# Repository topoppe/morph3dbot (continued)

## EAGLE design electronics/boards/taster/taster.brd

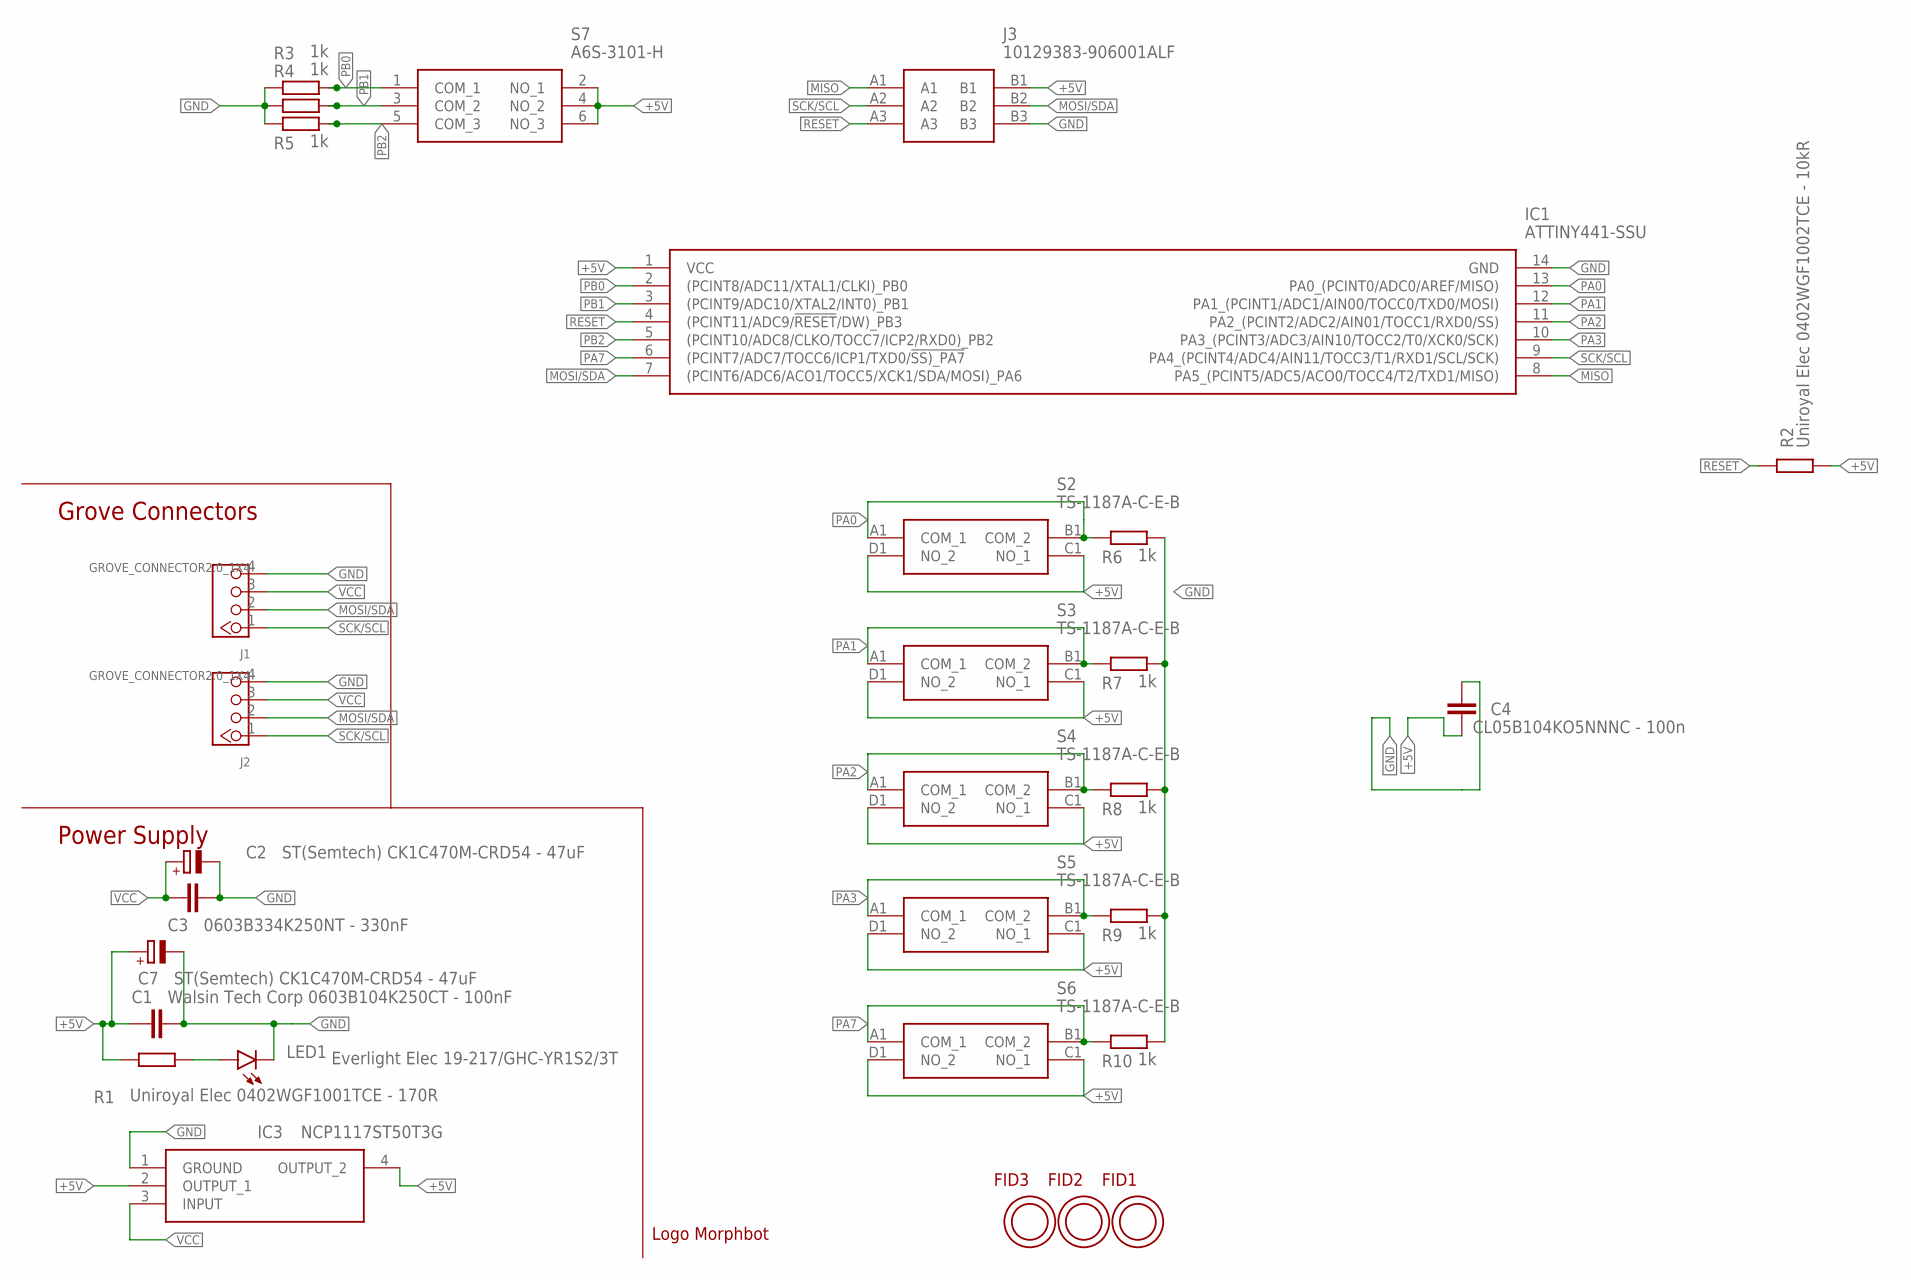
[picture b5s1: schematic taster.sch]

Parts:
C1: Walsin Tech Corp 0603B104K250CT - 100nF; C0603
C2, C7: ST(Semtech) CK1C470M-CRD54 - 47uF; PANASONIC_C
C3: 0603B334K250NT - 330nF; C0603
C4: CL05B104KO5NNNC - 100n; C0402
FID1, FID2, FID3: OPEN-PNP-FIDUCIAL
IC1: ATTINY441-SSU; SOIC127P600X175-14N
IC3: NCP1117ST50T3G; SOT230P700X180-4N
J1, J2: GROVE_CONNECTOR2.0_1X4; 2.0_1X4_STRAIGHT
J3: 10129383-906001ALF; 10129383906001ALF
LED1: Everlight Elec 19-217/GHC-YR1S2/3T; CHIPLED_0603
R1: Uniroyal Elec 0402WGF1001TCE - 170R; R0402
R2: Uniroyal Elec 0402WGF1002TCE - 10kR; R0402
R3, R4, R5, R6, R7, R8, R9, R10: 1k; R0402
S2, S3, S4, S5, S6: TS-1187A-C-E-B; TS1187ACEB
S7: A6S-3101-H; A6S3104H
U$1: LOGO_MORPHBOT5MM; LOGO_MORPHBOT

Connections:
+5V: C1.1, C4.1, C7.+, IC1.1 (VCC), IC3.2 (OUTPUT_1), IC3.4 (OUTPUT_2), J3.B1, R1.2, R2.2, S2.C1 (NO_1), S2.D1 (NO_2), S3.C1 (NO_1), S3.D1 (NO_2), S4.C1 (NO_1), S4.D1 (NO_2), S5.C1 (NO_1), S5.D1 (NO_2), S6.C1 (NO_1), S6.D1 (NO_2), S7.2 (NO_1), S7.4 (NO_2), S7.6 (NO_3)
GND: C1.2, C2.-, C3.1, C4.2, C7.-, IC1.14 (GND), IC3.1 (GROUND), J1.4, J2.4, J3.B3, LED1.C, R3.2, R4.2, R5.2, R6.1, R7.1, R8.1, R9.1, R10.1
MISO: IC1.8 (PA5_(PCINT5/ADC5/ACO0/TOCC4/T2/TXD1/MIS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), J3.A1
MOSI/SDA: IC1.7 ((PCINT6/ADC6/ACO1/TOCC5/XCK1/SDA/MOSI)_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), J1.2, J2.2, J3.B2
unnamed: LED1.A, R1.1
PA0: IC1.13 (PA0_(PCINT0/ADC0/AREF/MISO)), R6.2, S2.A1 (COM_1), S2.B1 (COM_2)
PA1: IC1.12 (PA1_(PCINT1/ADC1/AIN00/TOCC0/TXD0/MOSI)), R7.2, S3.A1 (COM_1), S3.B1 (COM_2)
PA2: IC1.11 (PA2_(PCINT2/ADC2/AIN01/TOCC1/RXD0/SS)), R8.2, S4.A1 (COM_1), S4.B1 (COM_2)
PA3: IC1.10 (PA3_(PCINT3/ADC3/AIN10/TOCC2/T0/XCK0/SC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), R9.2, S5.A1 (COM_1), S5.B1 (COM_2)
PA7: IC1.6 ((PCINT7/ADC7/TOCC6/ICP1/TXD0/!SS)_PA7), R10.2, S6.A1 (COM_1), S6.B1 (COM_2)
PB0: IC1.2 ((PCINT8/ADC11/XTAL1/CLKI)_PB0), R3.1, S7.1 (COM_1)
PB1: IC1.3 ((PCINT9/ADC10/XTAL2/INT0)_PB1), R4.1, S7.3 (COM_2)
PB2: IC1.5 ((PCINT10/ADC8/CLKO/TOCC7/ICP2/RXD0)_PB2), R5.1, S7.5 (COM_3)
RESET: IC1.4 ((PCINT11/ADC9/!RESET!/DW)_PB3), J3.A3, R2.1
SCK/SCL: IC1.9 (PA4_(PCINT4/ADC4/AIN11/TOCC3/T1/RXD1/SC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), J1.1, J2.1, J3.A2
VCC: C2.+, C3.2, IC3.3 (INPUT), J1.3, J2.3

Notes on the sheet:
Power Supply
Grove Connectors

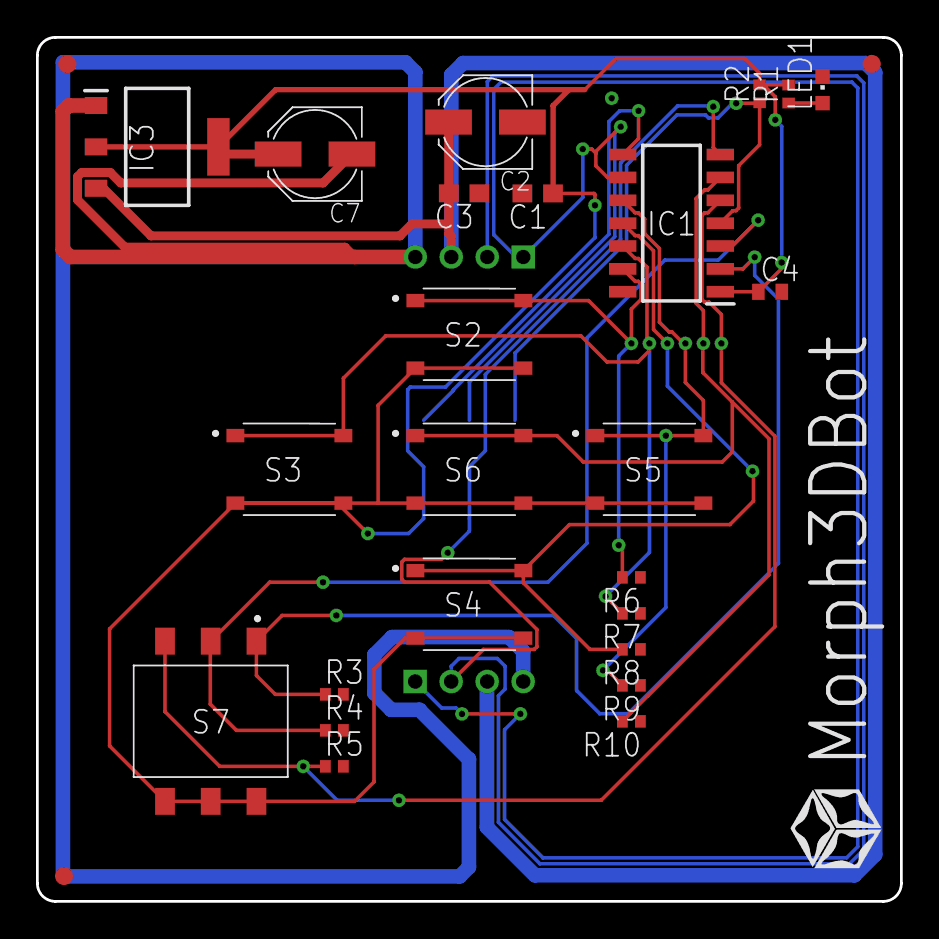
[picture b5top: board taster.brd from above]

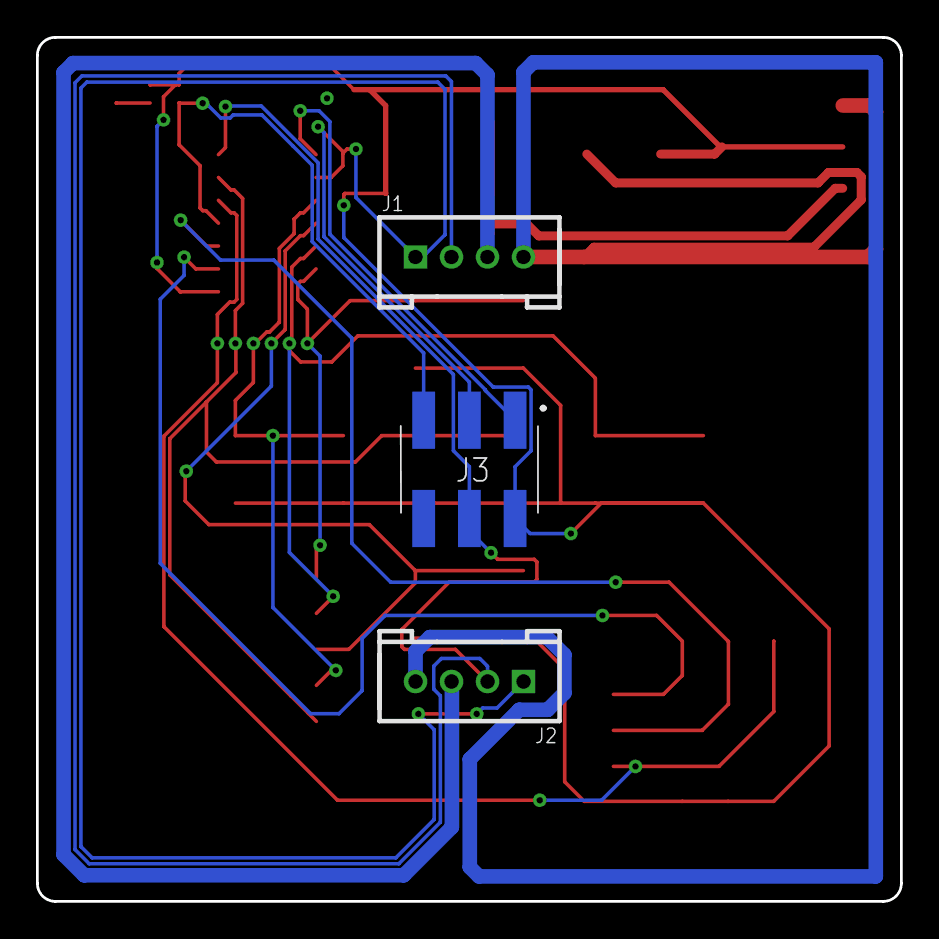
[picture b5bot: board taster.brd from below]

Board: 2 copper layers, 48.0 x 48.0 mm, 31 parts (3 on the bottom side), 16 nets.

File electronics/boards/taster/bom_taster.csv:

"Qty";"Value";"Device";"Package";"Parts";"Description";"ARROW_PART_NUMBER";"ARROW_PRICE-STOCK";"DESCRIPTION";"HEIGHT";"MANUFACTURER_NAME";"MANUFACTURER_PART_NUMBER";"MOUSER_PART_NUMBER";"MOUSER_PRICE-STOCK";"POPULARITY";"SPICEPREFIX";
"1";"0603B334K250NT - 330nF";"C-EUC0603";"C0603";"C3";"CAPACITOR, European symbol";"";"";"";"";"";"";"";"";"73";"C";
"1";"10129383-906001ALF";"10129383-906001ALF";"10129383906001ALF";"J3";"Headers & Wire Housings ECONOSTIK HEADER DR VT SMT 2X3";"10129383-906001ALF";"https://www.arrow.com/en/products/10129383-906001alf/amphenol-fci";"Headers & Wire Housings ECONOSTIK HEADER DR VT SMT 2X3";"8.58mm";"Amphenol";"10129383-906001ALF";"649-1012938390601ALF";"https://www.mouser.co.uk/ProductDetail/Amphenol-FCI/10129383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";"";"";
"8";"1k";"R-EU_R0402";"R0402";"R3, R4, R5, R6, R7, R8, R9, R10";"RESISTOR, European symbol";"";"";"";"";"";"";"";"";"0";"R";
"1";"A6S-3101-H";"A6S-3101-H";"A6S3104H";"S7";"3 Way Surface Mount DIP Switch 3P";"";"";"3 Way Surface Mount DIP Switch 3P";"4.5mm";"Omron Electronics";"A6S-3101-H";"653-A6S-3101-H";"https://www.mouser.co.uk/ProductDetail/Omron-Electronics/A6S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";"";"";
"1";"ATTINY441-SSU";"ATTINY441-SSU";"SOIC127P600X175-14N";"IC1";"8-bit Microcontrollers - MCU 16MHz 0.150" 14 SOIC";"ATTINY441-SSU";"https://www.arrow.com/en/products/attiny441-ssu/microchip-te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";"8-bit Microcontrollers - MCU 16MHz 0.150" 14 SOIC";"1.75mm";"Microchip";"ATTINY441-SSU";"556-ATTINY441-SSU";"https://www.mouser.co.uk/ProductDetail/Microchip-Technology-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";"";"";
"1";"CL05B104KO5NNNC - 100n";"C-EUC0402";"C0402";"C4";"CAPACITOR, European symbol";"";"";"";"";"";"";"";"";"18";"C";
"1";"Everlight Elec 19-217/GHC-YR1S2/3T";"LEDCHIPLED_0603";"CHIPLED_0603";"LED1";"LED";"";"";"";"";"";"";"";"";"28";"";
"2";"GROVE_CONNECTOR2.0_1X4";"GROVE_CONNECTOR2.0_1X4";"2.0_1X4_STRAIGHT";"J1, J2";"Seeedstudio Grove-Connector:";"";"";"";"";"";"";"";"";"";"";
"1";"LOGO_MORPHBOT5MM";"LOGO_MORPHBOT5MM";"LOGO_MORPHBOT";"U$1";"";"";"";"";"";"";"";"";"";"";"";
"1";"NCP1117ST50T3G";"NCP1117ST50T3G";"SOT230P700X180-4N";"IC3";"ON SEMICONDUCTOR - NCP1117ST50T3G - LDO, REG, 20VIN, 1A, 5V, 1%, SOT223-3";"NCP1117ST50T3G";"https://www.arrow.com/en/products/ncp1117st50t3g/on-semiconductor";"ON SEMICONDUCTOR - NCP1117ST50T3G - LDO, REG, 20VIN, 1A, 5V, 1%, SOT223-3";"1.8mm";"ON Semiconductor";"NCP1117ST50T3G";"863-NCP1117ST50T3G";"https://www.mouser.co.uk/ProductDetail/ON-Semiconductor/NCP1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";"";"";
"3";"OPEN-PNP-FIDUCIAL";"OPEN-PNP-FIDUCIAL";"OPEN-PNP-FIDUCIAL";"FID1, FID2, FID3";"";"";"";"";"";"";"";"";"";"";"";
"2";"ST(Semtech) CK1C470M-CRD54 - 47uF";"CPOL-EUC";"PANASONIC_C";"C2, C7";"POLARIZED CAPACITOR, European symbol";"";"";"";"";"";"";"";"";"4";"C";
"5";"TS-1187A-C-E-B";"TS-1187A-C-E-B";"TS1187ACEB";"S2, S3, S4, S5, S6";"SPST 50mA @ 12VDC 5.10mm x 5.10mm SMD Tactile Switches RoHS";"";"";"SPST 50mA @ 12VDC 5.10mm x 5.10mm SMD Tactile Switches RoHS";"1.65mm";"XKB Enterprise";"TS-1187A-C-E-B";"611-PTS526SK15SMR2L";"";"";"";
"1";"Uniroyal Elec 0402WGF1001TCE - 170R";"R-EU_R0402";"R0402";"R1";"RESISTOR, European symbol";"";"";"";"";"";"";"";"";"0";"R";
"1";"Uniroyal Elec 0402WGF1002TCE - 10kR";"R-EU_R0402";"R0402";"R2";"RESISTOR, European symbol";"";"";"";"";"";"";"";"";"0";"R";
"1";"Walsin Tech Corp 0603B104K250CT - 100nF";"C-EUC0603";"C0603";"C1";"CAPACITOR, European symbol";"";"";"";"";"";"";"";"";"73";"C";

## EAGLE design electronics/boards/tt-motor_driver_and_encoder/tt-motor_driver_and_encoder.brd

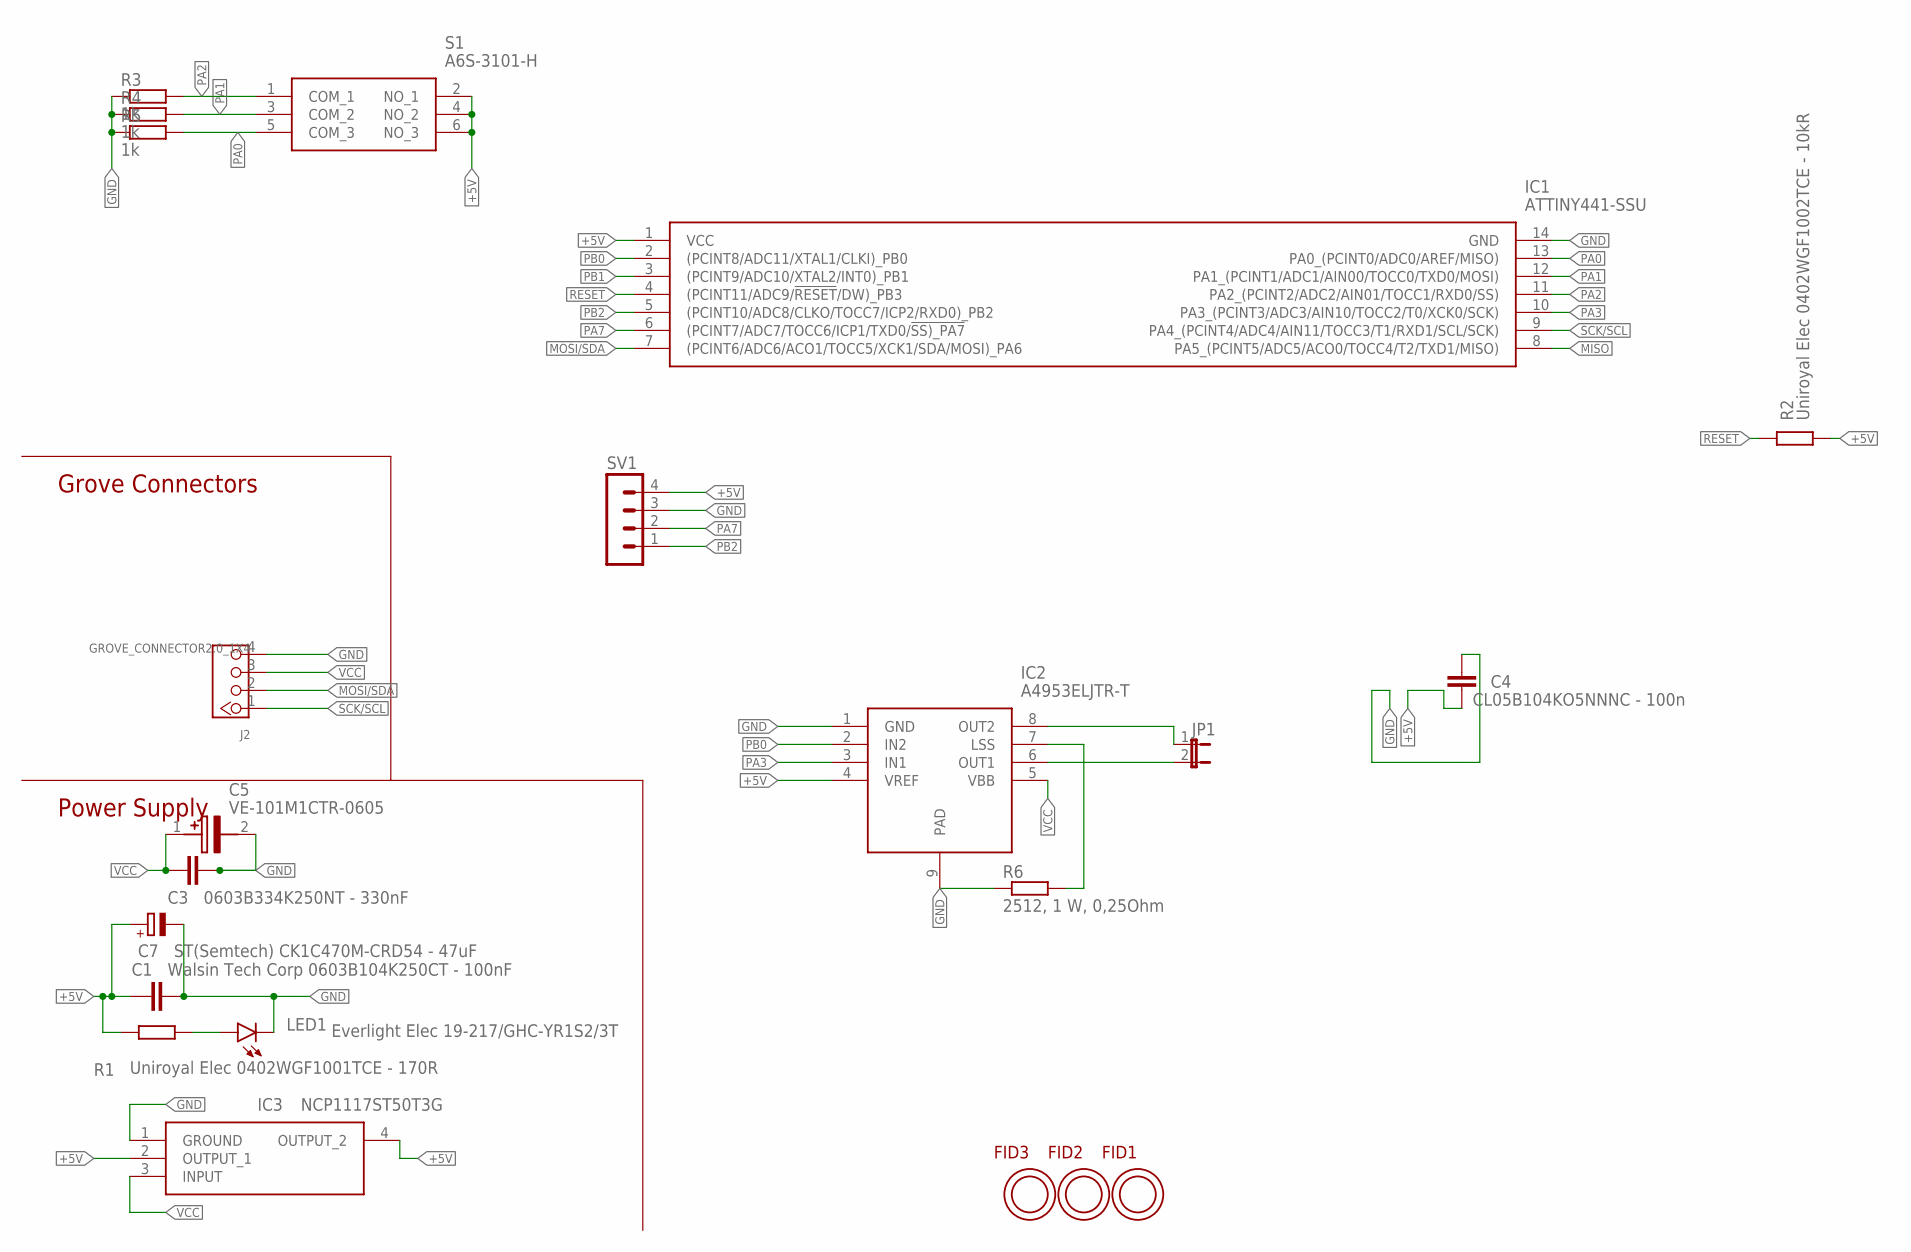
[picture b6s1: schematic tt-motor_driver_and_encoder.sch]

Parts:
C1: Walsin Tech Corp 0603B104K250CT - 100nF; C0603
C3: 0603B334K250NT - 330nF; C0603
C4: CL05B104KO5NNNC - 100n; C0402
C5: VE-101M1CTR-0605; CAPAE660X550N
C7: ST(Semtech) CK1C470M-CRD54 - 47uF; PANASONIC_C
FID1, FID2, FID3: OPEN-PNP-FIDUCIAL
IC1: ATTINY441-SSU; SOIC127P600X175-14N
IC2: A4953ELJTR-T; SOIC127P600X170-9N
IC3: NCP1117ST50T3G; SOT230P700X180-4N
J2: GROVE_CONNECTOR2.0_1X4; 2.0_1X4_STRAIGHT
JP1: JP1E; JP1
LED1: Everlight Elec 19-217/GHC-YR1S2/3T; CHIPLED_0603
R1: Uniroyal Elec 0402WGF1001TCE - 170R; R0402
R2: Uniroyal Elec 0402WGF1002TCE - 10kR; R0402
R3, R4, R5: 1k; R0402
R6: 2512, 1 W, 0,25Ohm; R2512
S1: A6S-3101-H; A6S3104H
SV1: MA04-1

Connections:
+5V: C1.1, C4.1, C7.+, IC1.1 (VCC), IC2.4 (VREF), IC3.2 (OUTPUT_1), IC3.4 (OUTPUT_2), R1.2, R2.2, S1.2 (NO_1), S1.4 (NO_2), S1.6 (NO_3), SV1.4
GND: C1.2, C3.1, C4.2, C5.2 (-), C7.-, IC1.14 (GND), IC2.1 (GND), IC2.9 (PAD), IC3.1 (GROUND), J2.4, LED1.C, R3.1, R4.1, R5.1, R6.1, SV1.3
MISO: IC1.8 (PA5_(PCINT5/ADC5/ACO0/TOCC4/T2/TXD1/MIS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)
MOSI/SDA: IC1.7 ((PCINT6/ADC6/ACO1/TOCC5/XCK1/SDA/MOSI)_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), J2.2
unnamed: LED1.A, R1.1
unnamed: IC2.6 (OUT1), JP1.2
unnamed: IC2.8 (OUT2), JP1.1
unnamed: IC2.7 (LSS), R6.2
PA0: IC1.13 (PA0_(PCINT0/ADC0/AREF/MISO)), R5.2, S1.5 (COM_3)
PA1: IC1.12 (PA1_(PCINT1/ADC1/AIN00/TOCC0/TXD0/MOSI)), R4.2, S1.3 (COM_2)
PA2: IC1.11 (PA2_(PCINT2/ADC2/AIN01/TOCC1/RXD0/SS)), R3.2, S1.1 (COM_1)
PA3: IC1.10 (PA3_(PCINT3/ADC3/AIN10/TOCC2/T0/XCK0/SC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), IC2.3 (IN1)
PA7: IC1.6 ((PCINT7/ADC7/TOCC6/ICP1/TXD0/!SS)_PA7), SV1.2
PB0: IC1.2 ((PCINT8/ADC11/XTAL1/CLKI)_PB0), IC2.2 (IN2)
PB1: IC1.3 ((PCINT9/ADC10/XTAL2/INT0)_PB1)
PB2: IC1.5 ((PCINT10/ADC8/CLKO/TOCC7/ICP2/RXD0)_PB2), SV1.1
RESET: IC1.4 ((PCINT11/ADC9/!RESET!/DW)_PB3), R2.1
SCK/SCL: IC1.9 (PA4_(PCINT4/ADC4/AIN11/TOCC3/T1/RXD1/SC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), J2.1
VCC: C3.2, C5.1 (+), IC2.5 (VBB), IC3.3 (INPUT), J2.3

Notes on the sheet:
Power Supply
Grove Connectors

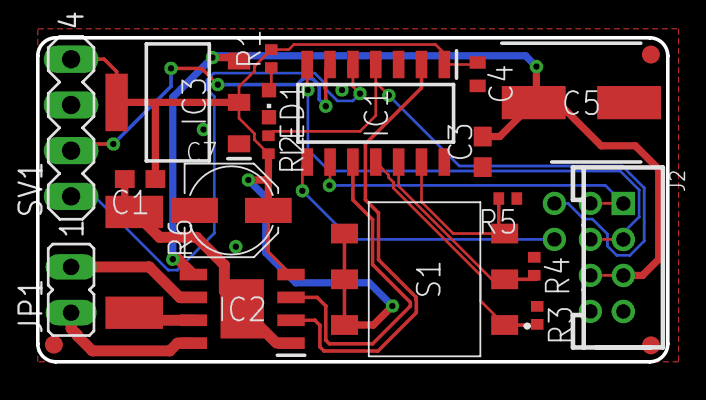
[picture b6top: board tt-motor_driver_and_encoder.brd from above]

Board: 2 copper layers, 35.0 x 18.0 mm, 22 parts (0 on the bottom side), 17 nets.

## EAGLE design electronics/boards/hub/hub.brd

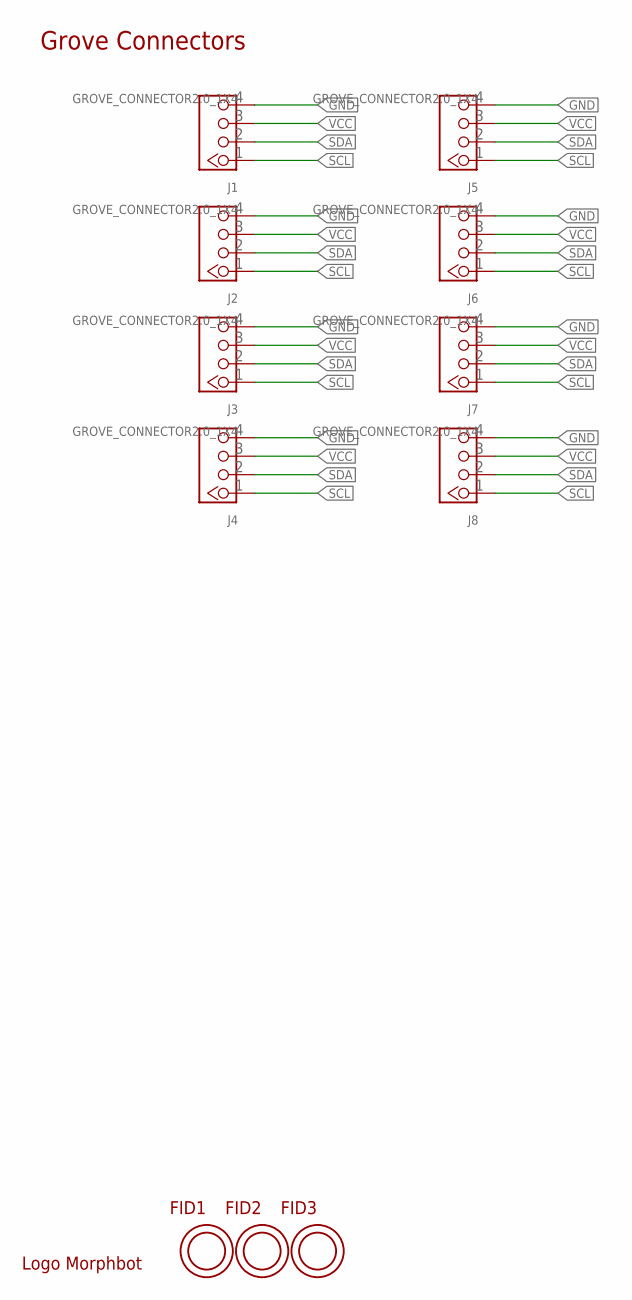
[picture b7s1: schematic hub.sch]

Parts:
FID1, FID2, FID3: OPEN-PNP-FIDUCIAL
J1, J2, J3, J4, J5, J6, J7, J8: GROVE_CONNECTOR2.0_1X4; 2.0_1X4_STRAIGHT
U$1: LOGO_MORPHBOT5MM; LOGO_MORPHBOT

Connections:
GND: J1.4, J2.4, J3.4, J4.4, J5.4, J6.4, J7.4, J8.4
SCL: J1.1, J2.1, J3.1, J4.1, J5.1, J6.1, J7.1, J8.1
SDA: J1.2, J2.2, J3.2, J4.2, J5.2, J6.2, J7.2, J8.2
VCC: J1.3, J2.3, J3.3, J4.3, J5.3, J6.3, J7.3, J8.3

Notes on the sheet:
Grove Connectors

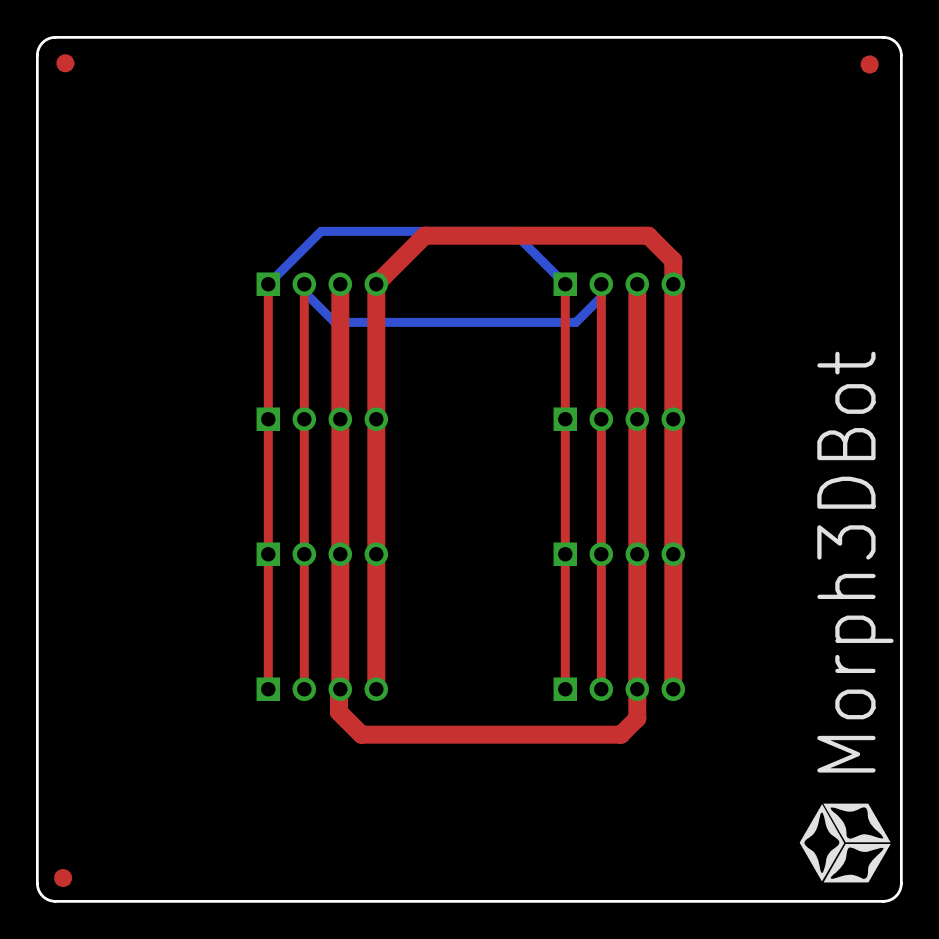
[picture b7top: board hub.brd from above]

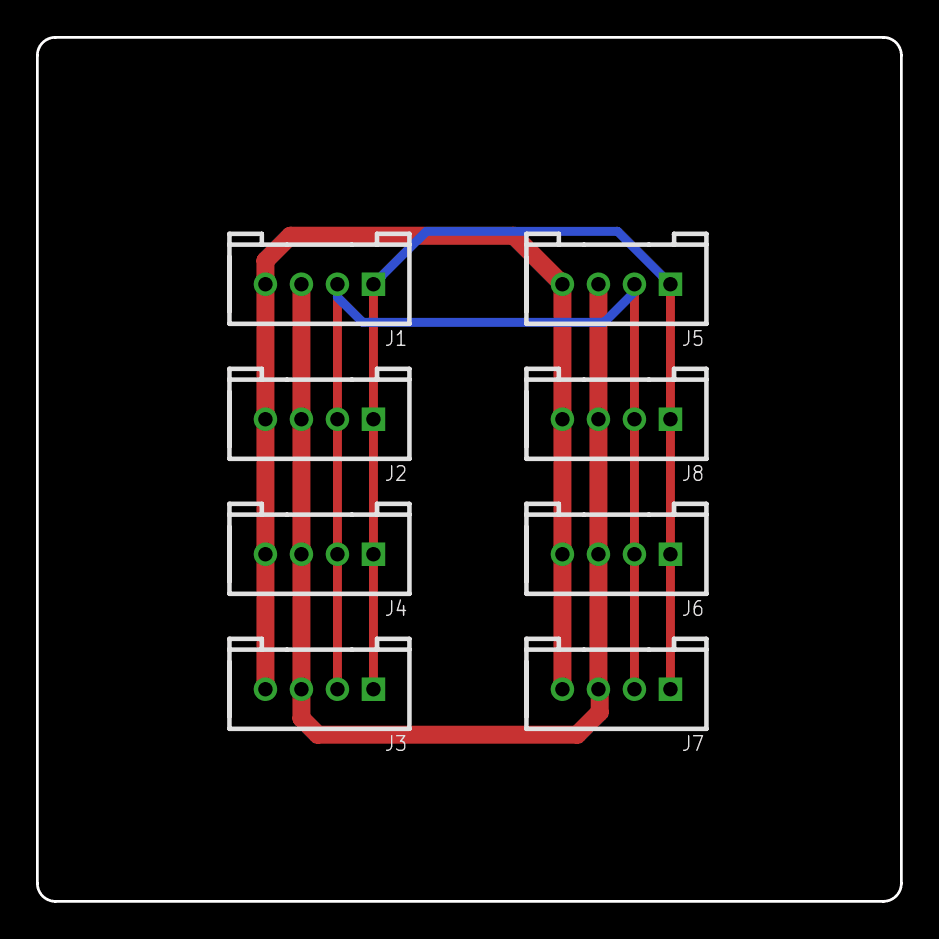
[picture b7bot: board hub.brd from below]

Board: 2 copper layers, 48.0 x 48.0 mm, 12 parts (8 on the bottom side), 4 nets.

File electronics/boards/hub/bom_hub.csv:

"Qty";"Value";"Device";"Package";"Parts";"Description";"";
"8";"GROVE_CONNECTOR2.0_1X4";"GROVE_CONNECTOR2.0_1X4";"2.0_1X4_STRAIGHT";"J1, J2, J3, J4, J5, J6, J7, J8";"Seeedstudio Grove-Connector:";"";
"1";"LOGO_MORPHBOT5MM";"LOGO_MORPHBOT5MM";"LOGO_MORPHBOT";"U$1";"";"";
"3";"OPEN-PNP-FIDUCIAL";"OPEN-PNP-FIDUCIAL";"OPEN-PNP-FIDUCIAL";"FID1, FID2, FID3";"";"";

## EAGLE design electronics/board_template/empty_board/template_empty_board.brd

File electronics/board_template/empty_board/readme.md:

# Empty-Board Template

Dieses Template dient als Vorlage für komplett eigene Designs.
Sie besitzt einen für das *Morph3DBot* passenden Form-Faktor. Bereiche auf der Unterseite, die nicht bestückt werden dürfen, sind eingezeichnet.

## Spannungsversorgung
Auf der Platine ist ein Linearregler verbaut. Er erzeugt aus der Versorgungsspannung des Systems eine stabile 5V Spannungsversorgung für den Controller sowie weitere Peripherie.

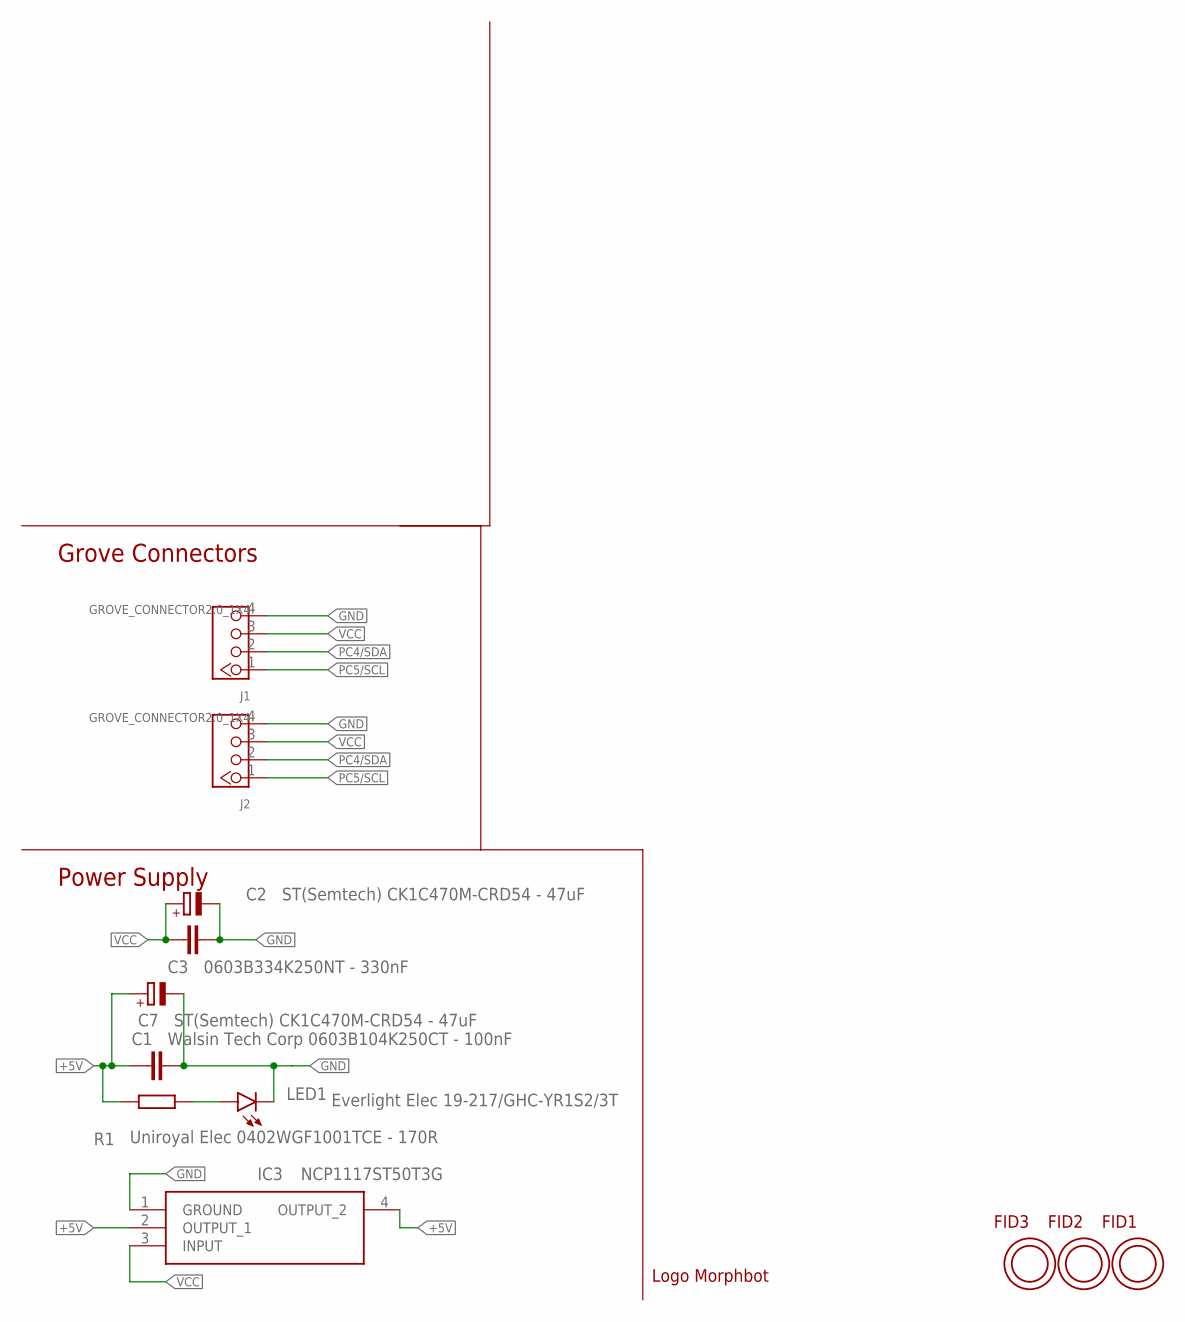
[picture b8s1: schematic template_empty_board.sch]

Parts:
C1: Walsin Tech Corp 0603B104K250CT - 100nF; C0603
C2, C7: ST(Semtech) CK1C470M-CRD54 - 47uF; PANASONIC_C
C3: 0603B334K250NT - 330nF; C0603
FID1, FID2, FID3: OPEN-PNP-FIDUCIAL
IC3: NCP1117ST50T3G; SOT230P700X180-4N
J1, J2: GROVE_CONNECTOR2.0_1X4; 2.0_1X4_STRAIGHT
LED1: Everlight Elec 19-217/GHC-YR1S2/3T; CHIPLED_0603
R1: Uniroyal Elec 0402WGF1001TCE - 170R; R0402
U$1: LOGO_MORPHBOT5MM; LOGO_MORPHBOT

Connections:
+5V: C1.1, C7.+, IC3.2 (OUTPUT_1), IC3.4 (OUTPUT_2), R1.2
GND: C1.2, C2.-, C3.1, C7.-, IC3.1 (GROUND), J1.4, J2.4, LED1.C
unnamed: LED1.A, R1.1
PC4/SDA: J1.2, J2.2
PC5/SCL: J1.1, J2.1
VCC: C2.+, C3.2, IC3.3 (INPUT), J1.3, J2.3

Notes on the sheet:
Power Supply
Grove Connectors

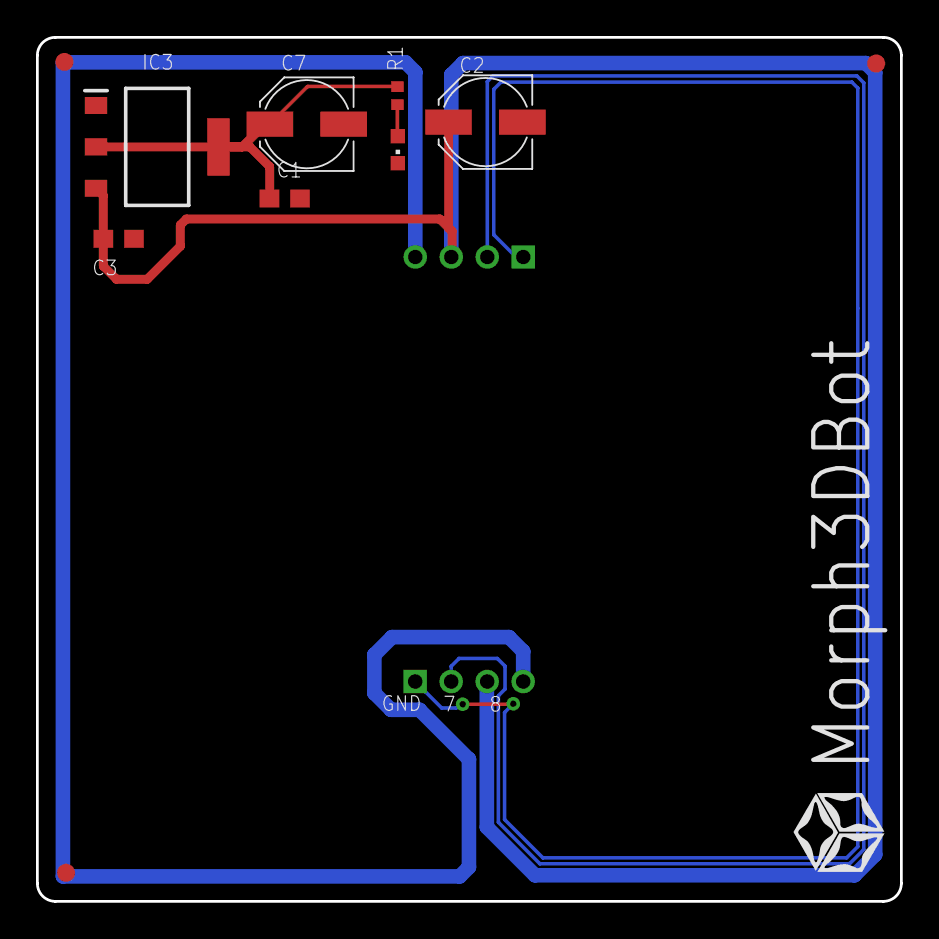
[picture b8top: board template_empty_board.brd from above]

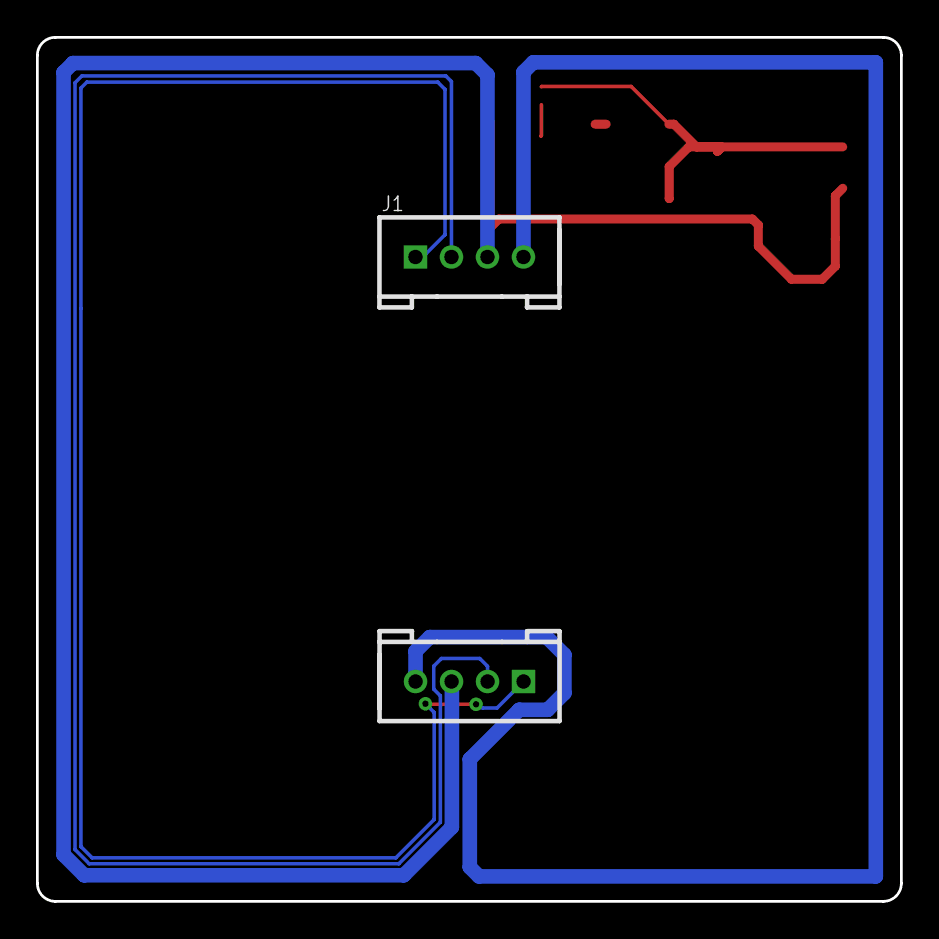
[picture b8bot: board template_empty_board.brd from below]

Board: 2 copper layers, 48.0 x 48.0 mm, 13 parts (2 on the bottom side), 6 nets.

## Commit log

2020-08-27 directory changed
2020-12-02 Templates für ATTiny44, ATMega328P und ESP hinzugefügt
2020-12-18 Stromversorgung und Hub fertig
2020-12-18 Stromversorgung beschriftung eingefügt
2020-12-18 Template Empty Board an anderen Linearregler angepasst
2021-01-02 Logo hinzugefügt
2021-01-02 attiny44 board dupliziert mit soic-14 package
2021-01-04 Fiducials eingefügt
2021-01-25 - mega328 Platine layout angepasst zum handlöten - Motorplatine eingefügt (2 DC oder 1 Stepper + 8 Servos)
2021-02-25 ESP32-Template: - USB-Datenleitungen getauscht (BugFix) 328P-Template: - USB-Datenleitungen getauscht (BugFix) - Reset-Leitung mit DTR verbunden (Zum Programieren über ARDUINO-IDE notwendig)
2021-03-22 Logo geändert
2021-03-22 Taster-Board eingefügt
2021-03-22 Ultrasonic-Platine eingefügt
2021-03-22 Line-Follower-Platine eingefügt
2021-03-23 TT-Motor-Board eingefügt
2021-03-23 TT-Motor-Board: Morphbot-Logo entfernt
2021-03-23 Mikrobus-Adapter-Board eingefügt
2021-03-23 - atmega-Platinen: Stop-Schicht angepasst auf Original - Attiny-Platinen: I2C-Leitungen korrigiert - CAM-Daten für alle Platinen erstellt
2021-04-06 -Bom-Listen aktualisiert - Readmes eingefügt
2021-04-06 typo
2021-04-06 Template readme eingefügt
2021-04-06 Ergänzung "empty Board"
2021-04-06 Readmes für ESP, ATTINY und EmptyBoard eingefügt
2021-04-06 Mehrere Readmes eingefügt
2021-04-06 Motor-Servo-Platine readme eingefügt
2021-04-06 TT-Motorplatine Readme eingefügt
2021-04-06 Haupt Readme geändert, ZIPs entfernt
